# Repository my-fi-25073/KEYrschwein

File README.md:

# Kirschwein
Kirschwein KBD PCB - RC-2XXX

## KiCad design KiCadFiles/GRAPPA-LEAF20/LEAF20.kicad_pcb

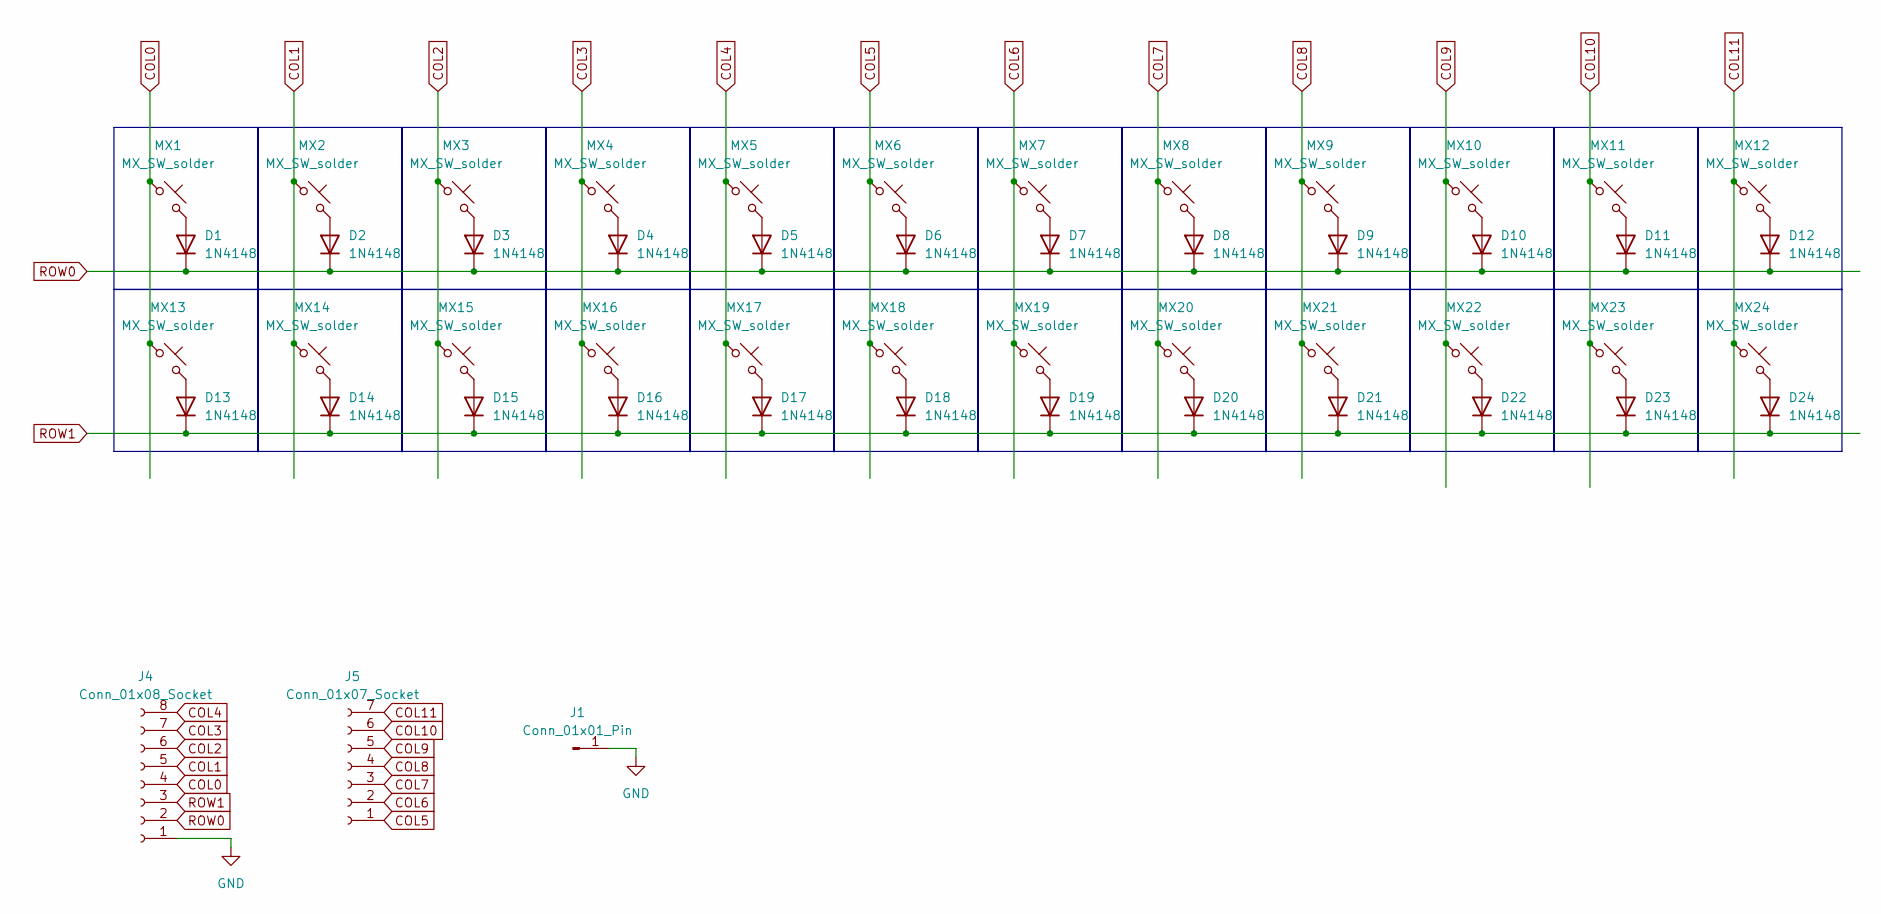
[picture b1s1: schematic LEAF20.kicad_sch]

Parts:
D1, D2, D3, D4, D5, D6, D7, D8, D9, D10, D11, D12, D13, D14, D15, D16, D17, D18, D19, D20, D21, D22, D23, D24: 1N4148; D_SOD-123-g
J1: Conn_01x01_Pin; SolderWire-0.75sqmm_1x01_D1.25mm_OD2.3mm
J4: Conn_01x08_Socket; JST_SH_SM08B-SRSS-TB_1x08-1MP_P1.00mm_Horizontal
J5: Conn_01x07_Socket; JST_SH_SM07B-SRSS-TB_1x07-1MP_P1.00mm_Horizontal
MX1, MX2, MX3, MX4, MX5, MX6, MX7, MX8, MX9, MX10, MX11, MX12, MX13, MX14, MX15, MX16, MX17, MX18, MX19, MX20, MX21, MX22, MX23, MX24: MX_SW_solder; SW_MX_1u

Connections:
COL0: J4.4, MX1.1, MX13.1
COL1: J4.5, MX2.1, MX14.1
COL2: J4.6, MX3.1, MX15.1
COL3: J4.7, MX4.1, MX16.1
COL4: J4.8, MX5.1, MX17.1
COL5: J5.1, MX6.1, MX18.1
COL6: J5.2, MX7.1, MX19.1
COL7: J5.3, MX8.1, MX20.1
COL8: J5.4, MX9.1, MX21.1
COL9: J5.5, MX10.1, MX22.1
COL10: J5.6, MX11.1, MX23.1
COL11: J5.7, MX12.1, MX24.1
GND: J1.1, J4.1
unnamed: D1.2 (A), MX1.2
unnamed: D2.2 (A), MX2.2
unnamed: D3.2 (A), MX3.2
unnamed: D4.2 (A), MX4.2
unnamed: D5.2 (A), MX5.2
unnamed: D6.2 (A), MX6.2
unnamed: D7.2 (A), MX7.2
unnamed: D8.2 (A), MX8.2
unnamed: D9.2 (A), MX9.2
unnamed: D10.2 (A), MX10.2
unnamed: D11.2 (A), MX11.2
unnamed: D12.2 (A), MX12.2
unnamed: D13.2 (A), MX13.2
unnamed: D14.2 (A), MX14.2
unnamed: D15.2 (A), MX15.2
unnamed: D16.2 (A), MX16.2
unnamed: D17.2 (A), MX17.2
unnamed: D18.2 (A), MX18.2
unnamed: D19.2 (A), MX19.2
unnamed: D20.2 (A), MX20.2
unnamed: D21.2 (A), MX21.2
unnamed: D22.2 (A), MX22.2
unnamed: D23.2 (A), MX23.2
unnamed: D24.2 (A), MX24.2
ROW0: D1.1 (K), D2.1 (K), D3.1 (K), D4.1 (K), D5.1 (K), D6.1 (K), D7.1 (K), D8.1 (K), D9.1 (K), D10.1 (K), D11.1 (K), D12.1 (K), J4.2
ROW1: D13.1 (K), D14.1 (K), D15.1 (K), D16.1 (K), D17.1 (K), D18.1 (K), D19.1 (K), D20.1 (K), D21.1 (K), D22.1 (K), D23.1 (K), D24.1 (K), J4.3

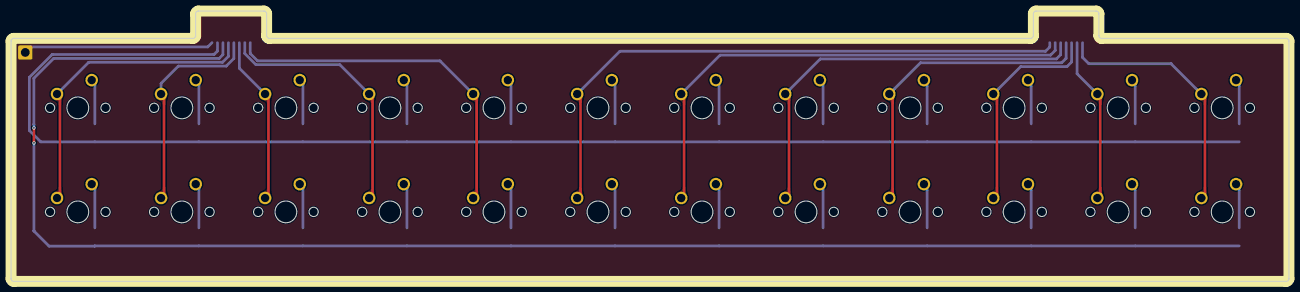
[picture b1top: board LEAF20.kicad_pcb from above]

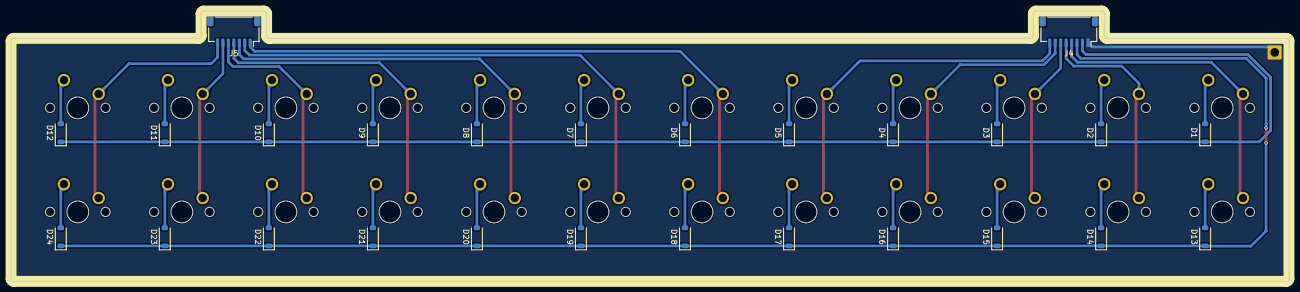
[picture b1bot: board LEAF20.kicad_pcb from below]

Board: 2 copper layers, 234.0 x 49.5 mm, 51 parts (27 on the bottom side), 39 nets.

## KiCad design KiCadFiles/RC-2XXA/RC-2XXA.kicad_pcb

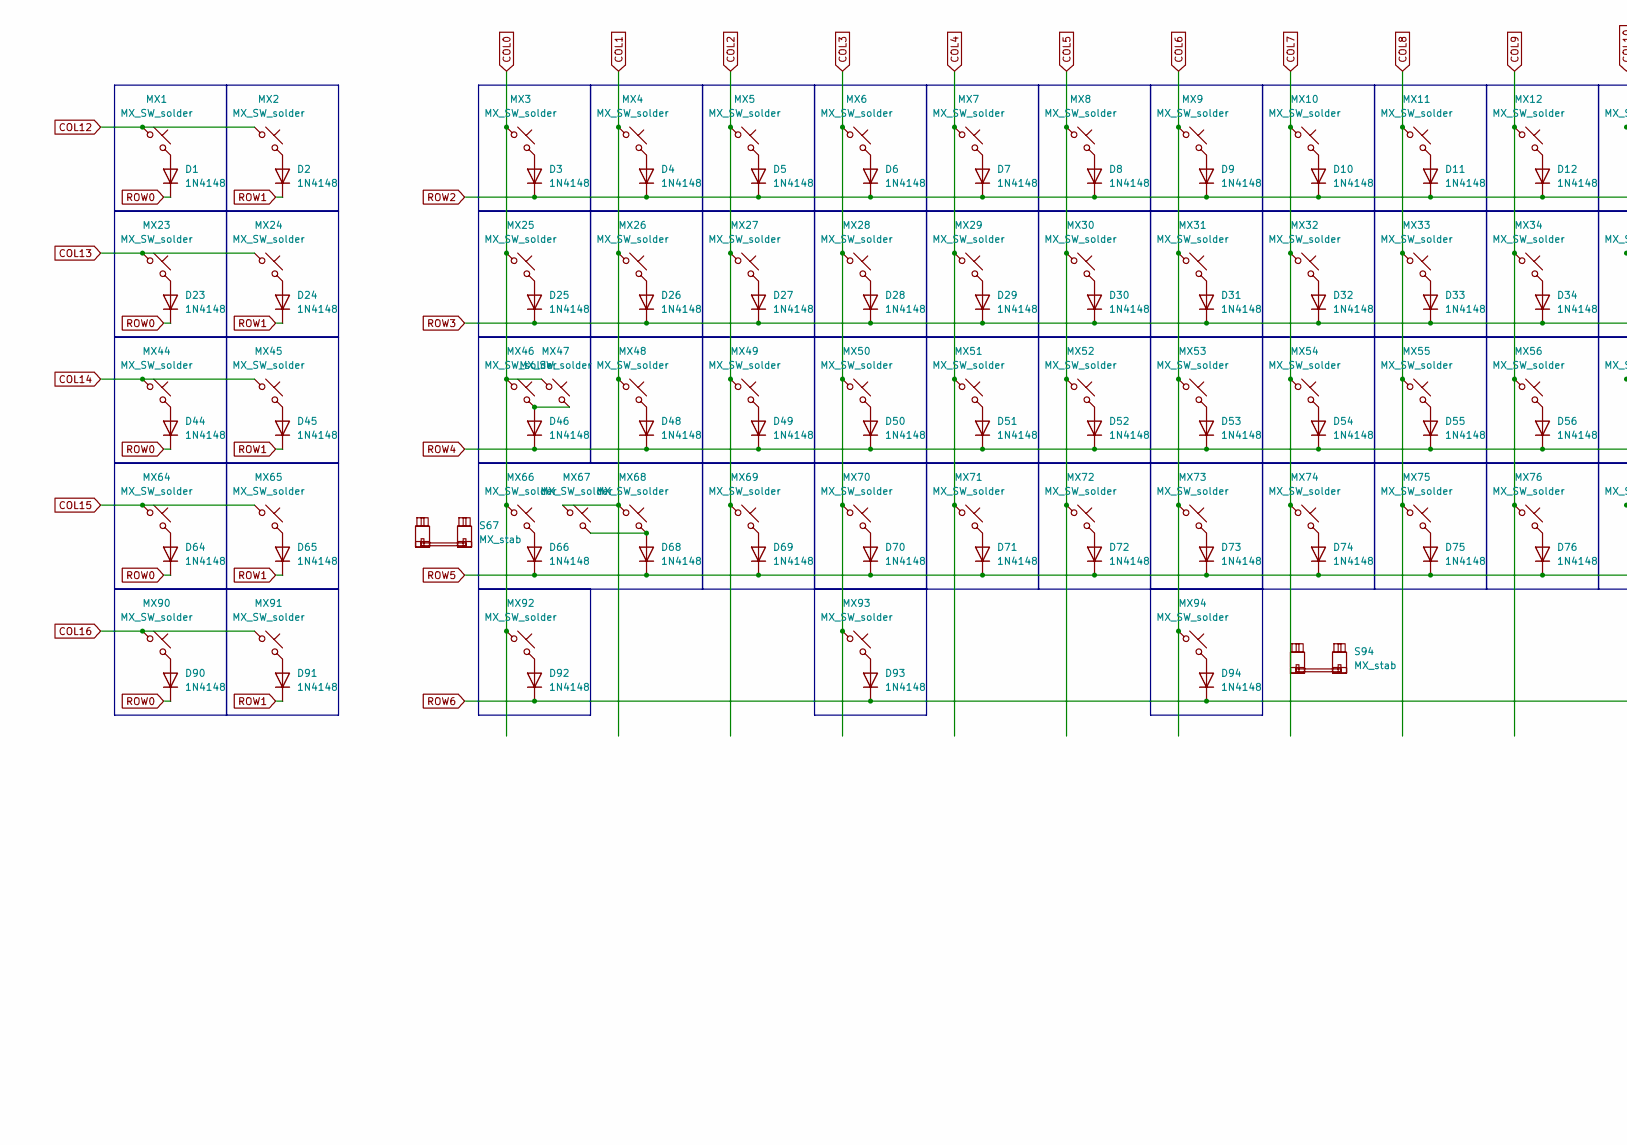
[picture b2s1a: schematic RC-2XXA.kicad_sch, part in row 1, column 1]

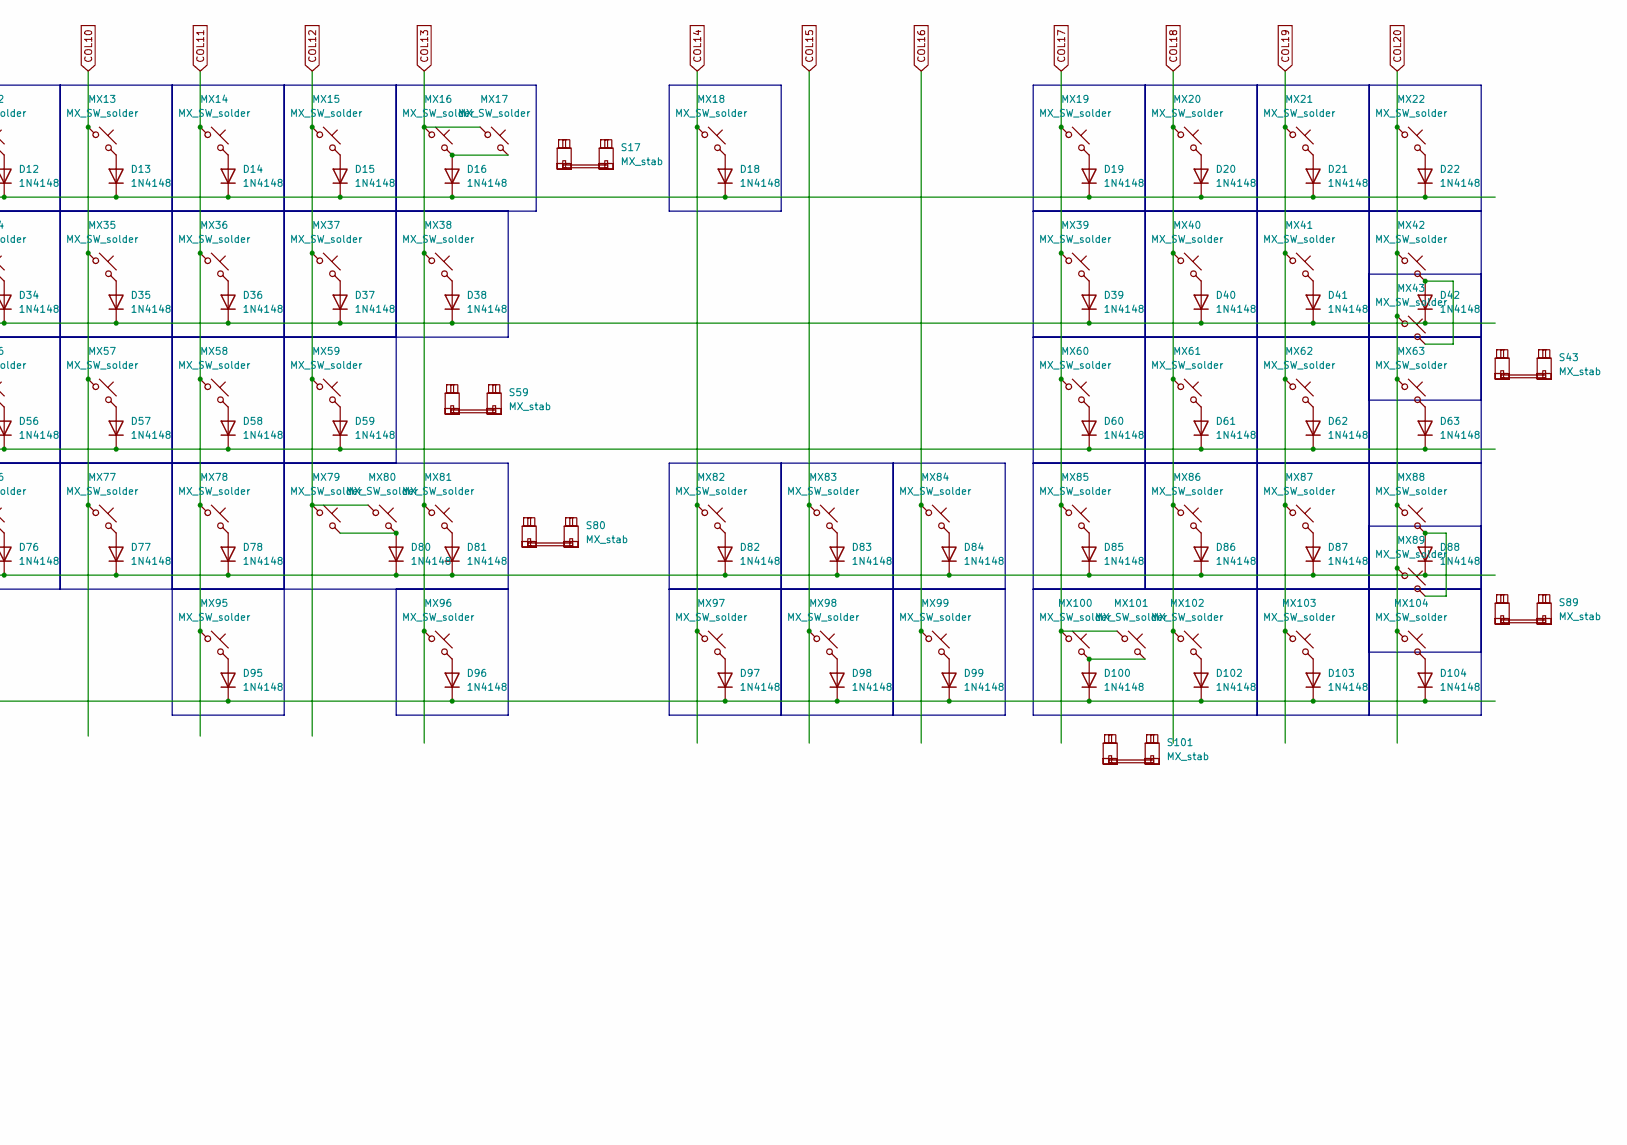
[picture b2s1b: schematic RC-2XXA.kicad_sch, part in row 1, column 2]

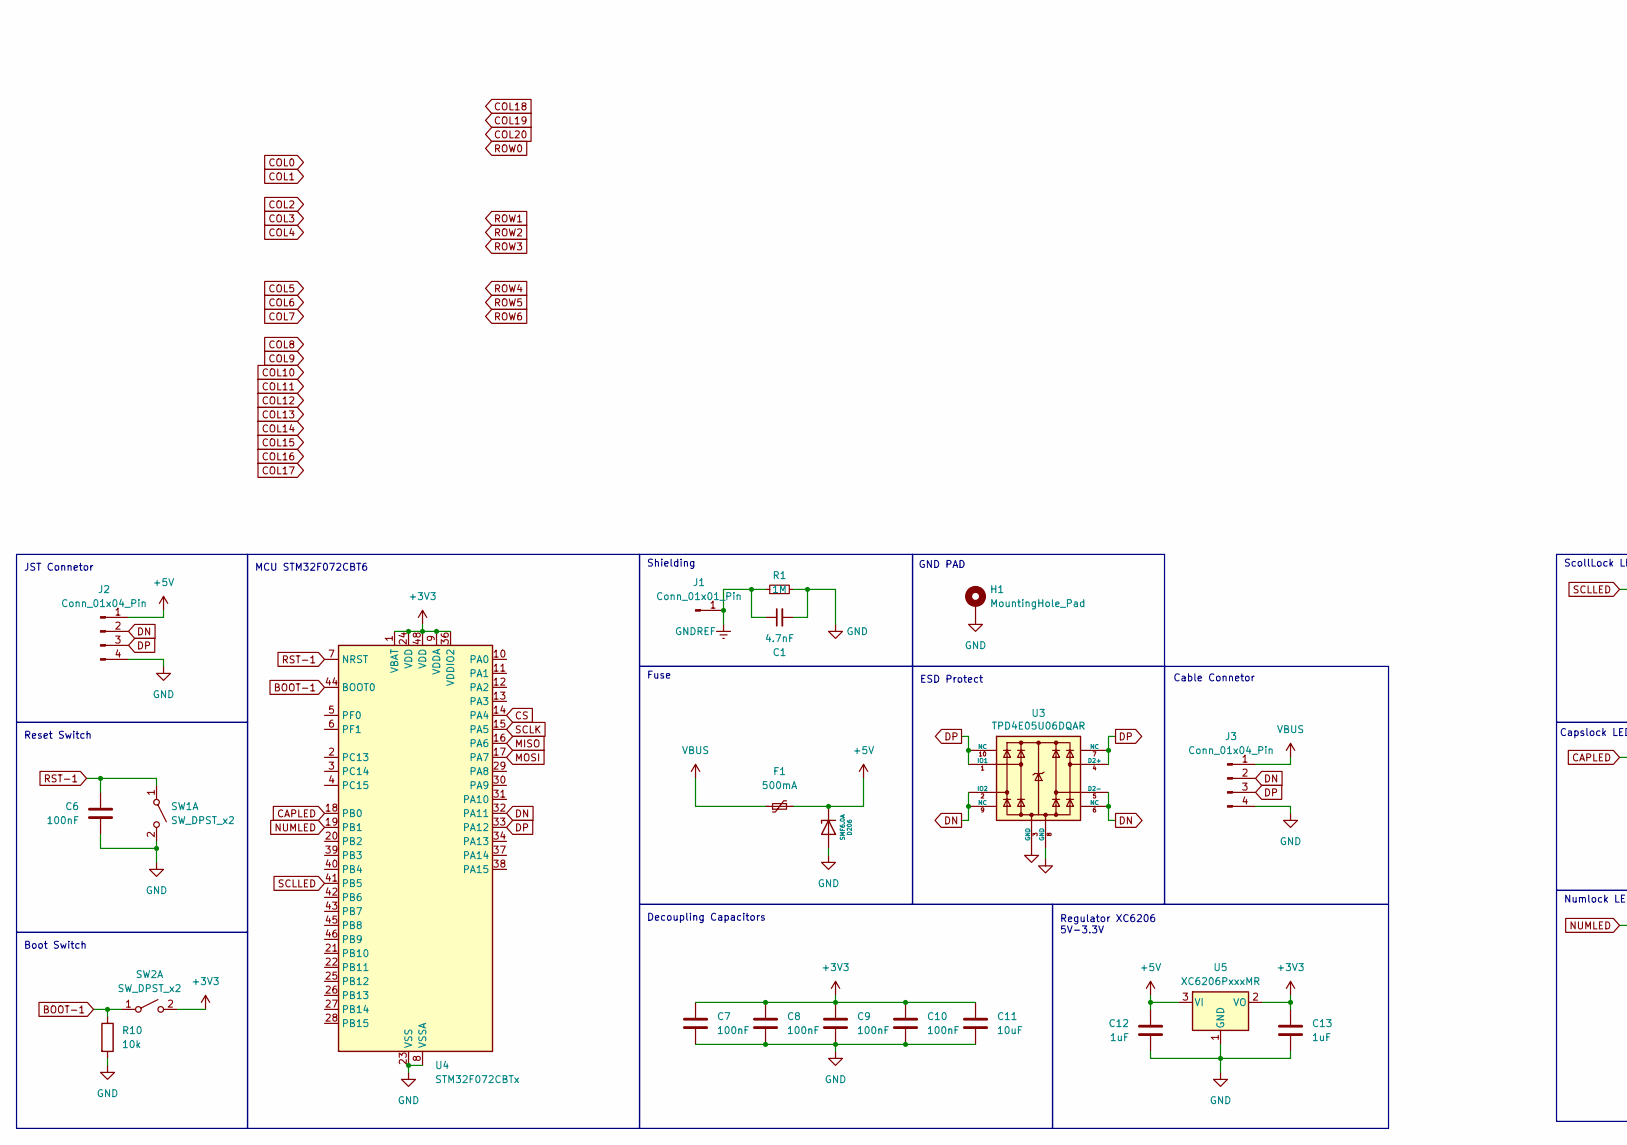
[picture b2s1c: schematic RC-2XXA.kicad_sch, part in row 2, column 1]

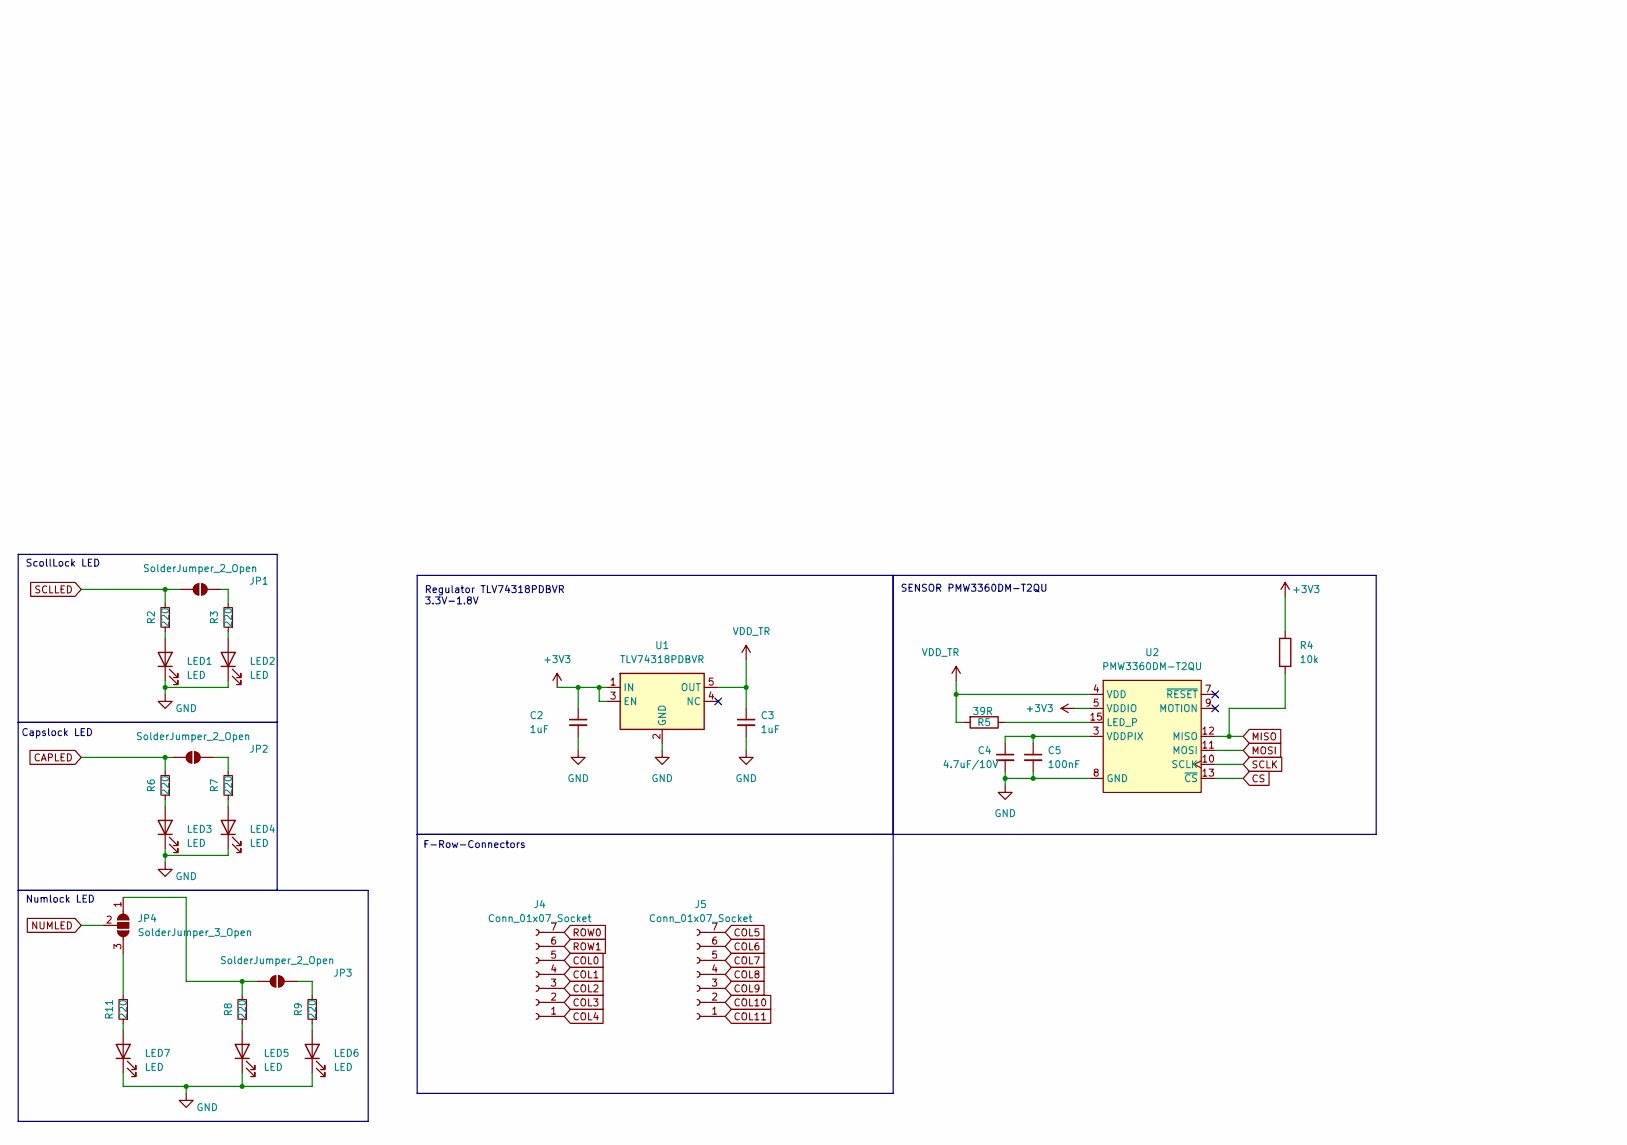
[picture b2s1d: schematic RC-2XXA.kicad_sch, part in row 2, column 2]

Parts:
C1: 4.7nF; C_0805_2012Metric_Pad1.18x1.45mm_HandSolder
C2, C3, C12, C13: 1uF; C_0805_2012Metric_Pad1.18x1.45mm_HandSolder
C4: 4.7uF/10V; C_0805_2012Metric_Pad1.18x1.45mm_HandSolder
C5, C6, C7, C8, C9, C10: 100nF; C_0805_2012Metric_Pad1.18x1.45mm_HandSolder
C11: 10uF; C_0805_2012Metric_Pad1.18x1.45mm_HandSolder
D1, D2, D3, D4, D5, D6, D7, D8, D9, D10, D11, D12, D13, D14, D15, D16, D18, D19, D20, D21, D22, D23, D24, D25, D26, D27, D28, D29, D30, D31, D32, D33, D34, D35, D36, D37, D38, D39, D40, D41, D42, D44, D45, D46, D48, D49, D50, D51, D52, D53, D54, D55, D56, D57, D58, D59, D60, D61, D62, D63, D64, D65, D66, D68, D69, D70, D71, D72, D73, D74, D75, D76, D77, D78, D80, D81, D82, D83, D84, D85, D86, D87, D88, D90, D91, D92, D93, D94, D95, D96, D97, D98, D99, D100, D102, D103, D104: 1N4148; D_SOD-123-g
D206: SMF6.0A; D_SOD-123; Manufacturer Part Number SMF6.0A; LCSC Part Number C708002
F1: 500mA; Fuse_1206_3216Metric; LCSC C70076
H1: MountingHole_Pad; Cherry-GND-PAD
J1: Conn_01x01_Pin; TestPoint_THTPad_2.0x2.0mm_Drill1.0mm
J2: Conn_01x04_Pin; JST_SH_SM04B-SRSS-TB_1x04-1MP_P1.00mm_Horizontal; MPN C160404
J3: Conn_01x04_Pin; My-SolderWire-0.5sqmm_1x04_D0.9mm_OD2.1mm
J4, J5: Conn_01x07_Socket; JST_SH_SM07B-SRSS-TB_1x07-1MP_P1.00mm_Horizontal
JP1, JP2, JP3: SolderJumper_2_Open; SolderJumper-2_P1.3mm_Open_RoundedPad1.0x1.5mm
JP4: SolderJumper_3_Open; SolderJumper-3_P1.3mm_Open_RoundedPad1.0x1.5mm
LED1, LED2, LED4, LED5, LED6, LED7: LED; DIP_LED_MX_3mm
LED3: LED; CAPS_LED_MX_3mm
MX1, MX2, MX3, MX4, MX5, MX6, MX7, MX8, MX9, MX10, MX11, MX12, MX13, MX14, MX15, MX16, MX17, MX18, MX19, MX20, MX21, MX22, MX23, MX24, MX26, MX27, MX28, MX29, MX30, MX31, MX32, MX33, MX34, MX35, MX36, MX37, MX39, MX40, MX41, MX42, MX43, MX44, MX45, MX48, MX49, MX50, MX51, MX52, MX53, MX54, MX55, MX56, MX57, MX58, MX59, MX60, MX61, MX62, MX63, MX64, MX65, MX66, MX67, MX69, MX70, MX71, MX72, MX73, MX74, MX75, MX76, MX77, MX78, MX80, MX81, MX82, MX83, MX84, MX85, MX86, MX87, MX88, MX89, MX90, MX91, MX94, MX97, MX98, MX99, MX100, MX101, MX102, MX103, MX104: MX_SW_solder; SW_MX_1u
MX25, MX38, MX92, MX93, MX95, MX96: MX_SW_solder; SW_MX_1.5u
MX46: MX_SW_solder; SW_MX_1.75u_STP_1.25
MX47, MX79: MX_SW_solder; SW_MX_1.75u
MX68: MX_SW_solder; SW_MX_1.25u
R1: 1M; R_0805_2012Metric_Pad1.20x1.40mm_HandSolder
R2, R3, R6, R7, R8, R9, R11: 220; R_0805_2012Metric_Pad1.20x1.40mm_HandSolder
R4, R10: 10k; R_0805_2012Metric_Pad1.20x1.40mm_HandSolder
R5: 39R; R_0805_2012Metric_Pad1.20x1.40mm_HandSolder
S17, S43, S89, S101: MX_stab; STAB_MX_2u
S59, S67: MX_stab; STAB_MX_2.25u
S80: MX_stab; STAB_MX_2.75u
S94: MX_stab; STAB_MX_7u
SW1, SW2: SW_DPST_x2; SW_Push_1P1T_XKB_TS-1187A; MPN C318884
U1: TLV74318PDBVR; SOT-23-5; MPN C485152
U2: PMW3360DM-T2QU; TrackballHolder_34mm
U3: TPD4E05U06DQAR; USON-10_2.5x1.0mm_P0.5mm; Manufacturer Part Number TPD4E05U06DQAR; LCSC Part Number C138714
U4: STM32F072CBTx; LQFP-48_7x7mm_P0.5mm; MPN C81720
U5: XC6206PxxxMR; SOT-23-3; MPN C5148692

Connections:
+3V3: C2.1, C7.1, C8.1, C9.1, C10.1, C11.1, C13.1, R4.1, SW2.2 (B), U1.1 (IN), U1.3 (EN), U2.5 (VDDIO), U4.1 (VBAT), U4.9 (VDDA), U4.24 (VDD), U4.36 (VDDIO2), U4.48 (VDD), U5.2 (VO)
+5V: C12.1, D206.1 (K), F1.2, J2.1, U5.3 (VI)
BOOT-1: R10.1, SW2.1 (A), U4.44 (BOOT0)
CAPLED: JP2.1 (A), R6.2, U4.18 (PB0)
COL0: J4.5, MX3.1, MX25.1, MX46.1, MX47.1, MX66.1, MX92.1
COL1: J4.4, MX4.1, MX26.1, MX48.1, MX67.1, MX68.1
COL2: J4.3, MX5.1, MX27.1, MX49.1, MX69.1
COL3: J4.2, MX6.1, MX28.1, MX50.1, MX70.1, MX93.1
COL4: J4.1, MX7.1, MX29.1, MX51.1, MX71.1
COL5: J5.7, MX8.1, MX30.1, MX52.1, MX72.1
COL6: J5.6, MX9.1, MX31.1, MX53.1, MX73.1, MX94.1
COL7: J5.5, MX10.1, MX32.1, MX54.1, MX74.1
COL8: J5.4, MX11.1, MX33.1, MX55.1, MX75.1
COL9: J5.3, MX12.1, MX34.1, MX56.1, MX76.1
COL10: J5.2, MX13.1, MX35.1, MX57.1, MX77.1
COL11: J5.1, MX14.1, MX36.1, MX58.1, MX78.1, MX95.1
COL12: MX1.1, MX2.1, MX15.1, MX37.1, MX59.1, MX79.1, MX80.1
COL13: MX16.1, MX17.1, MX23.1, MX24.1, MX38.1, MX81.1, MX96.1
COL14: MX18.1, MX44.1, MX45.1, MX82.1, MX97.1
COL15: MX64.1, MX65.1, MX83.1, MX98.1
COL16: MX84.1, MX90.1, MX91.1, MX99.1
COL17: MX19.1, MX39.1, MX60.1, MX85.1, MX100.1, MX101.1
COL18: MX20.1, MX40.1, MX61.1, MX86.1, MX102.1
COL19: MX21.1, MX41.1, MX62.1, MX87.1, MX103.1
COL20: MX22.1, MX42.1, MX43.1, MX63.1, MX88.1, MX89.1, MX104.1
CS: U2.13 (~CS), U4.14 (PA4)
DN: J2.2, J3.2, U3.2 (IO2), U3.5 (D2-), U3.6 (NC), U3.9 (NC), U4.32 (PA11)
DP: J2.3, J3.3, U3.1 (IO1), U3.4 (D2+), U3.7 (NC), U3.10 (NC), U4.33 (PA12)
GND: C1.2, C2.2, C3.2, C4.2, C5.2, C6.2, C7.2, C8.2, C9.2, C10.2, C11.2, C12.2, C13.2, D206.2 (A), H1.1, J2.4, J3.4, LED1.1 (K), LED2.1 (K), LED3.1 (K), LED4.1 (K), LED5.1 (K), LED6.1 (K), LED7.1 (K), R1.2, R10.2, SW1.2 (B), U1.2 (GND), U2.8 (GND), U3.3 (GND), U3.8 (GND), U4.8 (VSSA), U4.23 (VSS), U4.35 (VSS), U4.47 (VSS), U5.1 (GND)
GNDREF: C1.1, J1.1, R1.1
MISO: R4.2, U2.12 (MISO), U4.16 (PA6)
MOSI: U2.11 (MOSI), U4.17 (PA7)
NUMLED: JP4.2 (C), U4.19 (PB1)
unnamed: D1.2 (A), MX1.2
unnamed: D2.2 (A), MX2.2
unnamed: D3.2 (A), MX3.2
unnamed: D4.2 (A), MX4.2
unnamed: D5.2 (A), MX5.2
unnamed: D6.2 (A), MX6.2
unnamed: D7.2 (A), MX7.2
unnamed: D8.2 (A), MX8.2
unnamed: D9.2 (A), MX9.2
unnamed: D10.2 (A), MX10.2
unnamed: D11.2 (A), MX11.2
unnamed: D12.2 (A), MX12.2
unnamed: D13.2 (A), MX13.2
unnamed: D14.2 (A), MX14.2
unnamed: D15.2 (A), MX15.2
unnamed: D16.2 (A), MX16.2, MX17.2
unnamed: D18.2 (A), MX18.2
unnamed: D19.2 (A), MX19.2
unnamed: D20.2 (A), MX20.2
unnamed: D21.2 (A), MX21.2
unnamed: D22.2 (A), MX22.2
unnamed: D23.2 (A), MX23.2
unnamed: D24.2 (A), MX24.2
unnamed: D25.2 (A), MX25.2
unnamed: D26.2 (A), MX26.2
unnamed: D27.2 (A), MX27.2
unnamed: D28.2 (A), MX28.2
unnamed: D29.2 (A), MX29.2
unnamed: D30.2 (A), MX30.2
unnamed: D31.2 (A), MX31.2
unnamed: D32.2 (A), MX32.2
unnamed: D33.2 (A), MX33.2
unnamed: D34.2 (A), MX34.2
unnamed: D35.2 (A), MX35.2
unnamed: D36.2 (A), MX36.2
unnamed: D37.2 (A), MX37.2
unnamed: D38.2 (A), MX38.2
unnamed: D39.2 (A), MX39.2
unnamed: D40.2 (A), MX40.2
unnamed: D41.2 (A), MX41.2
unnamed: D42.2 (A), MX42.2, MX43.2
unnamed: D44.2 (A), MX44.2
unnamed: D45.2 (A), MX45.2
unnamed: D46.2 (A), MX46.2, MX47.2
unnamed: D48.2 (A), MX48.2
unnamed: D49.2 (A), MX49.2
unnamed: D50.2 (A), MX50.2
unnamed: D51.2 (A), MX51.2
unnamed: D52.2 (A), MX52.2
unnamed: D53.2 (A), MX53.2
unnamed: D54.2 (A), MX54.2
unnamed: D55.2 (A), MX55.2
unnamed: D56.2 (A), MX56.2
unnamed: D57.2 (A), MX57.2
unnamed: D58.2 (A), MX58.2
unnamed: D59.2 (A), MX59.2
unnamed: D60.2 (A), MX60.2
unnamed: D61.2 (A), MX61.2
unnamed: D62.2 (A), MX62.2
unnamed: D63.2 (A), MX63.2
unnamed: D64.2 (A), MX64.2
unnamed: D65.2 (A), MX65.2
unnamed: D66.2 (A), MX66.2
unnamed: D68.2 (A), MX67.2, MX68.2
unnamed: D69.2 (A), MX69.2
unnamed: D70.2 (A), MX70.2
unnamed: D71.2 (A), MX71.2
unnamed: D72.2 (A), MX72.2
unnamed: D73.2 (A), MX73.2
unnamed: D74.2 (A), MX74.2
unnamed: D75.2 (A), MX75.2
unnamed: D76.2 (A), MX76.2
unnamed: D77.2 (A), MX77.2
unnamed: D78.2 (A), MX78.2
unnamed: D80.2 (A), MX79.2, MX80.2
unnamed: D81.2 (A), MX81.2
unnamed: D82.2 (A), MX82.2
unnamed: D83.2 (A), MX83.2
unnamed: D84.2 (A), MX84.2
unnamed: D85.2 (A), MX85.2
unnamed: D86.2 (A), MX86.2
unnamed: D87.2 (A), MX87.2
unnamed: D88.2 (A), MX88.2, MX89.2
unnamed: D90.2 (A), MX90.2
unnamed: D91.2 (A), MX91.2
unnamed: D92.2 (A), MX92.2
unnamed: D93.2 (A), MX93.2
unnamed: D94.2 (A), MX94.2
unnamed: D95.2 (A), MX95.2
unnamed: D96.2 (A), MX96.2
unnamed: D97.2 (A), MX97.2
unnamed: D98.2 (A), MX98.2
unnamed: D99.2 (A), MX99.2
unnamed: D100.2 (A), MX100.2, MX101.2
unnamed: D102.2 (A), MX102.2
unnamed: D103.2 (A), MX103.2
unnamed: D104.2 (A), MX104.2
unnamed: JP1.2 (B), R3.2
unnamed: JP2.2 (B), R7.2
unnamed: JP3.1 (A), JP4.1 (A), R8.2
unnamed: JP3.2 (B), R9.2
unnamed: JP4.3 (B), R11.2
unnamed: LED1.2 (A), R2.1
unnamed: LED2.2 (A), R3.1
unnamed: LED3.2 (A), R6.1
unnamed: LED4.2 (A), R7.1
unnamed: LED5.2 (A), R8.1
unnamed: LED6.2 (A), R9.1
unnamed: LED7.2 (A), R11.1
unnamed: R5.1, U2.15 (LED_P)
unnamed: C4.1, C5.1, U2.3 (VDDPIX)
ROW0: D1.1 (K), D23.1 (K), D44.1 (K), D64.1 (K), D90.1 (K), J4.7
ROW1: D2.1 (K), D24.1 (K), D45.1 (K), D65.1 (K), D91.1 (K), J4.6
ROW2: D3.1 (K), D4.1 (K), D5.1 (K), D6.1 (K), D7.1 (K), D8.1 (K), D9.1 (K), D10.1 (K), D11.1 (K), D12.1 (K), D13.1 (K), D14.1 (K), D15.1 (K), D16.1 (K), D18.1 (K), D19.1 (K), D20.1 (K), D21.1 (K), D22.1 (K)
ROW3: D25.1 (K), D26.1 (K), D27.1 (K), D28.1 (K), D29.1 (K), D30.1 (K), D31.1 (K), D32.1 (K), D33.1 (K), D34.1 (K), D35.1 (K), D36.1 (K), D37.1 (K), D38.1 (K), D39.1 (K), D40.1 (K), D41.1 (K), D42.1 (K)
ROW4: D46.1 (K), D48.1 (K), D49.1 (K), D50.1 (K), D51.1 (K), D52.1 (K), D53.1 (K), D54.1 (K), D55.1 (K), D56.1 (K), D57.1 (K), D58.1 (K), D59.1 (K), D60.1 (K), D61.1 (K), D62.1 (K), D63.1 (K)
ROW5: D66.1 (K), D68.1 (K), D69.1 (K), D70.1 (K), D71.1 (K), D72.1 (K), D73.1 (K), D74.1 (K), D75.1 (K), D76.1 (K), D77.1 (K), D78.1 (K), D80.1 (K), D81.1 (K), D82.1 (K), D83.1 (K), D84.1 (K), D85.1 (K), D86.1 (K), D87.1 (K), D88.1 (K)
ROW6: D92.1 (K), D93.1 (K), D94.1 (K), D95.1 (K), D96.1 (K), D97.1 (K), D98.1 (K), D99.1 (K), D100.1 (K), D102.1 (K), D103.1 (K), D104.1 (K)
RST-1: C6.1, SW1.1 (A), U4.7 (NRST)
SCLK: U2.10 (SCLK), U4.15 (PA5)
SCLLED: JP1.1 (A), R2.2, U4.41 (PB5)
VBUS: F1.1, J3.1
VDD_TR: C3.1, R5.2, U1.5 (OUT), U2.4 (VDD)

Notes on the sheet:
MCU STM32F072CBT6
Numlock LED
Cable Connetor
Shielding
ScollLock LED
Reset Switch
Decoupling Capacitors
Boot Switch
Regulator XC6206 5V-3.3V
JST Connetor
Capslock LED
SENSOR PMW3360DM-T2QU
ESD Protect
F-Row-Connectors
Regulator TLV74318PDBVR 3.3V-1.8V
Fuse
GND PAD

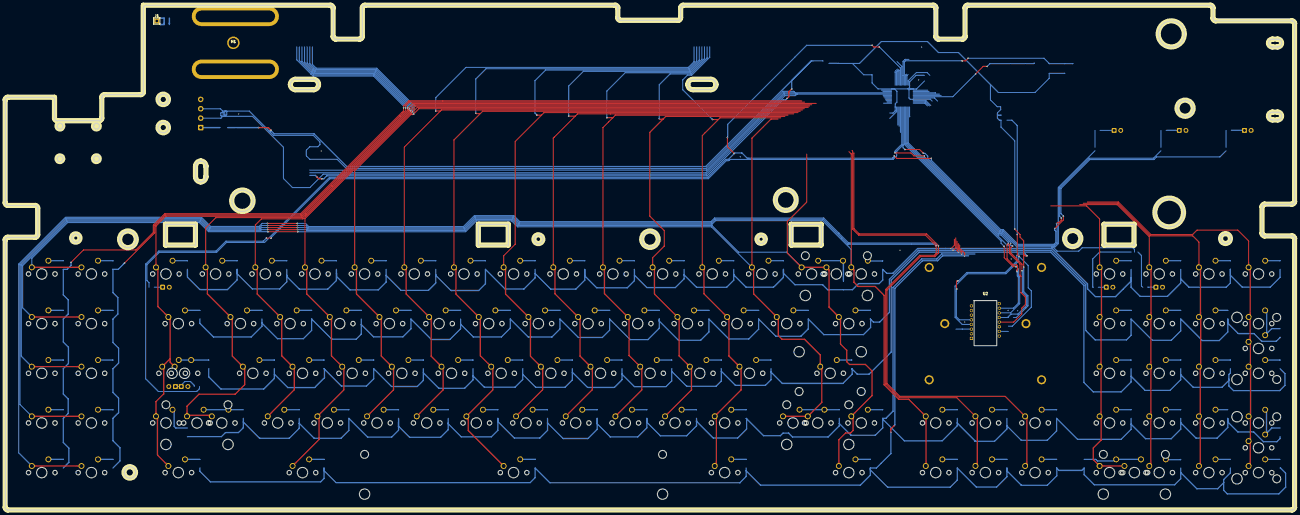
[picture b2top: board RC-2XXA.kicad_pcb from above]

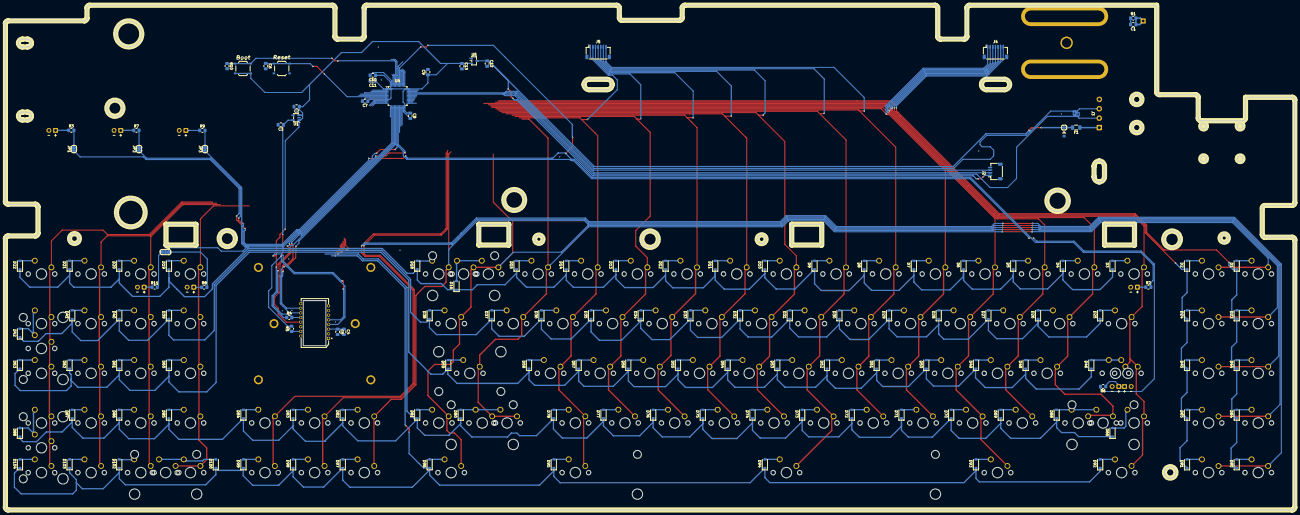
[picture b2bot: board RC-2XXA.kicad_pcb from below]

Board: 2 copper layers, 494.6 x 193.6 mm, 259 parts (137 on the bottom side), 156 nets.

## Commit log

2025-12-20 Add new DXF files: 2xxx-edge.dxf and frow-edge.dxf
2025-12-22 Add new KiCad project files for LEAF20, NAN40, TAN40, and RC-2XXX, including PCB, schematic, and project files. Update .gitignore to exclude keyautoplace.log files. Add JSON placer files for each pro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
2025-12-23 Add new KiCad project files for RC-2XXA, including PCB, schematic, and project files. Update existing schematic for RC-2XXX to adjust paper size and reposition components.
2026-02-09 Refactor KiCad project files for RC-2XXA: streamline net connections in PCB, adjust solder mask clearance in project settings, and add new connector symbols in schematic. Enhance error handling for u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
2026-02-10 Update rectangle positions in RC-2XXA schematic to correct alignment and spacing. Adjust multiple rectangle coordinates for improved layout consistency.
2026-02-10 Update .gitignore to exclude additional KiCad files for RC-2XXA, including production files and fabrication toolkit options.
2026-02-12 Update RC-2XXA KiCad files: adjust footprint properties, correct rectangle positions in schematic, and enhance error handling for pin connections. Remove unnecessary junctions and wires for improved 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
2026-02-12 Add Zener diode symbol to RC-2XXA schematic, update component references and footprints for capacitors and resistors, and correct wire connections for improved circuit clarity.
2026-02-12 Add netlist for RC-2XXA schematic, including detailed component specifications for capacitors and their properties. This file establishes the electrical connections and design parameters for the proj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
2026-02-17 updated pcb & sch
2026-02-17 feat(kicad): sync RC-2XXA schematic/PCB and add routing presets
2026-02-23 Refactor code structure for improved readability and maintainability
2026-02-24 Implement code changes to enhance functionality and improve performance
2026-02-27 Update RC-2XXA project files: Adjust minimum clearance and modify connector properties
    - Changed minimum clearance in RC-2XXA.kicad_pro from 0.5 to 0.26.
    - Updated the "Value" property of a component in RC-2XXA.kicad_sch from "VBUS" to "+5V".
    - Added a new connector symbol with detailed properties including reference, value, footprint, and description.
    - Removed the old connector symbol to avoid duplication.
2026-02-27 Add Solder Jumper component and associated wiring to RC-2XXA schematic
    - Introduced a new Solder Jumper component (JP) with properties including reference, value, footprint, and description.
    - Added multiple instances of the Solder Jumper at specified coordinates in the schematic.
    - Updated wiring to accommodate the new component, ensuring proper connections.
2026-03-01 Add Mounting Hole Pad and GND symbol to schematic
    - Introduced a new symbol for a mounting hole pad with properties including reference, value, footprint, and description.
    - Added a graphical representation of the mounting hole pad with a circle.
    - Included a GND symbol with properties for reference, value, and description, creating a global label for ground.
    - Updated the schematic layout to accommodate the new components.
2026-03-02 Add Solder Jumper and update component positions in schematic
    - Introduced a new Solder Jumper component (JP4) with properties and graphical representation.
    - Adjusted positions of several components including resistors (R8, R9, R11) and LEDs (LED6, LED7) for better layout.
    - Updated junctions and wire connections to reflect new component placements.
    - Removed redundant junctions and wires to clean up the schematic.
2026-03-07 Implement feature X to enhance user experience and fix bug Y in module Z
2026-03-10 Update design rule checks in RC-2XXA project configuration
    - Changed nonmirrored_text_on_back_layer check from "warning" to "ignore"
    - Updated silk-related checks (silk_edge_clearance, silk_over_copper, silk_overlap) from "warning" to "ignore"
2026-03-26 Add custom keycode functionality and VIA support for 900Than9 keyboard
    - Implemented custom keycodes for various OS shortcuts including language switch, screenshot, and desktop navigation.
    - Created key handler functions to manage keycode processing based on the operating system.
    - Added a header file defining custom keycodes and keymap layers.
    - Included a readme file with build and flashing instructions for the keyboard.
    - Configured rules.mk to enable VIA and OS detection features.
    - Added visual representation of the keyboard layout in vi.json and via.json files.
2026-03-26 Refactor VIA configuration for Keyrschwein keyboard
    - Updated keyboard name from "900Than9" to "Keyrschwein"
    - Changed product ID to "0x3333"
    - Modified matrix dimensions to 7 rows and 21 columns
    - Revised layout labels to include new split key options
    - Reworked keymap structure for improved layout representation
